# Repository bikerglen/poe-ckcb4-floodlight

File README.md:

# poe-ckcb4-floodlight
Power over Ethernet and Art-Net control for a Color Kinetics Colorburst 4 RGB LED floodlight

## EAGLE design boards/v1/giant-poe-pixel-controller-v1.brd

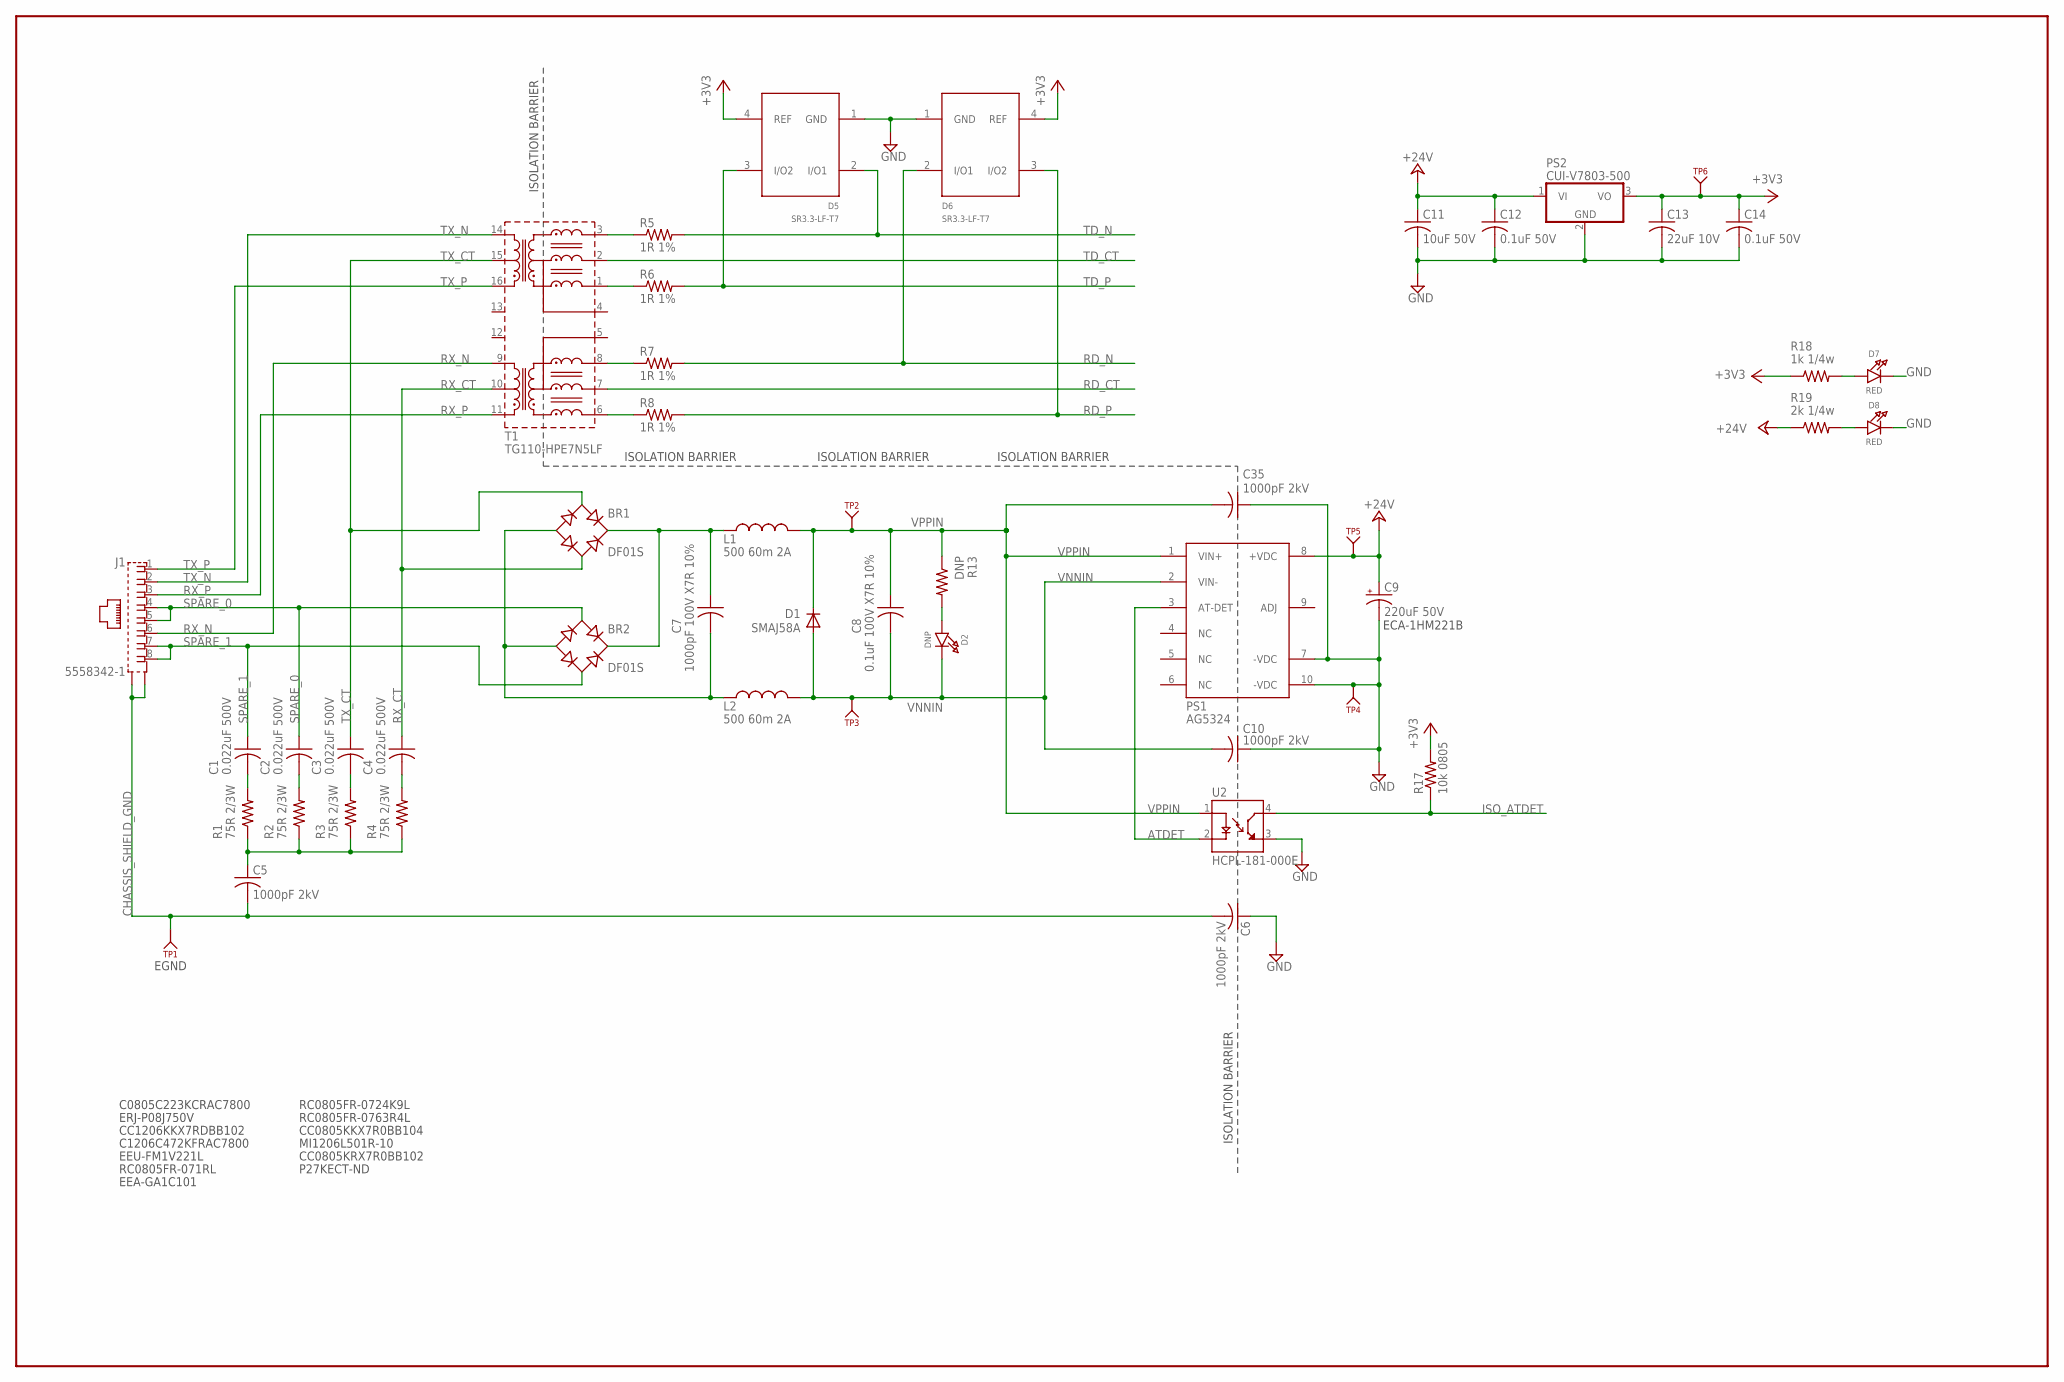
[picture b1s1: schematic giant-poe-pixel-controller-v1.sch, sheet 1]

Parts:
BR1, BR2: DF01S; DFS
C1, C2, C3, C4: 0.022uF 500V; C1206
C5, C6, C10, C35: 1000pF 2kV; C1206K
C7: 1000pF 100V X7R 10%; C0805
C8: 0.1uF 100V X7R 10%; C0805
C9: 220uF 50V; E5-10,5
C11: 10uF 50V; C1210K; MFR_PART_NO C1210C106K5RACTU
C12, C14: 0.1uF 50V; C0805; MFR_PART_NO C1206S104M5RACTU
C13: 22uF 10V; C1206K; MFR_PART_NO C1206C226K8RAC7800
D1: SMAJ58A; DO214AC
D2: DNP; CHIPLED_0805_NOOUTLINE
D5, D6: SR3.3-LF-T7; SOT143B
D7, D8: RED; CHIPLED_0805_NOOUTLINE
J1: 5558342-1; TE_5558342-1
L1, L2: 500 60m 2A; L3216C
PS1: AG5324
PS2: CUI-V7803-500; CUI-78XX-500
R1, R2, R3, R4: 75R 2/3W; R1206
R5, R6, R7, R8: 1R 1%; R0805
R13: DNP; R1206
R17: 10k 0805; R0805
R18: 1k 1/4w; R0805
R19: 2k 1/4w; R0805
T1: TG110-HPE7N5LF; RP-ULTRA
TP1, TP2, TP3, TP4, TP5, TP6: KEYSTONE_500X; KEYSTONE_TP500X
U2: HCPL-181-000E; SOIC254P675X240-4N

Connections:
+3V3: C13.1, C14.1, D5.4 (REF), D6.4 (REF), PS2.3 (VO), R17.2, R18.1, TP6.1; also elsewhere on the board
+24V: C9.+, C11.1, C12.1, PS1.8 (+VDC), PS2.1 (VI), R19.1, TP5.1; also elsewhere on the board
ATDET: PS1.3 (AT-DET), U2.2 (CATHODE)
CHASSIS_SHIELD_GND: C5.2, C6.2, J1.SH1 (S1), J1.SH2 (S2), TP1.1
GND: C6.1, C9.-, C10.1, C11.2, C12.2, C13.2, C14.2, C35.1, D5.1 (GND), D6.1 (GND), D7.C, D8.C, PS1.7 (-VDC), PS1.10 (-VDC), PS2.2 (GND), TP4.1, U2.3 (EMITTER); also elsewhere on the board
ISO_ATDET: R17.1, U2.4 (COLLECTOR); also elsewhere on the board
unnamed: BR1.+, BR2.+, C7.1, L1.1
unnamed: R5.1, T1.3
unnamed: BR1.-, BR2.-, C7.2, L2.1
unnamed: R6.1, T1.1
unnamed: C4.2, R4.2
unnamed: R7.1, T1.8
unnamed: D2.A, R13.2
unnamed: R8.1, T1.6
unnamed: C1.2, R1.2
unnamed: C2.2, R2.2
unnamed: C3.2, R3.2
unnamed: C5.1, R1.1, R2.1, R3.1, R4.1
unnamed: D7.A, R18.2
unnamed: D8.A, R19.2
RD_CT: T1.7; also elsewhere on the board
RD_N: D6.2 (I/O1), R7.2; also elsewhere on the board
RD_P: D6.3 (I/O2), R8.2; also elsewhere on the board
RX_CT: BR1.AC2, C4.1, T1.10
RX_N: J1.6, T1.9
RX_P: J1.3, T1.11
SPARE_0: BR2.AC1, C2.1, J1.4, J1.5
SPARE_1: BR2.AC2, C1.1, J1.7, J1.8
TD_CT: T1.2; also elsewhere on the board
TD_N: D5.2 (I/O1), R5.2; also elsewhere on the board
TD_P: D5.3 (I/O2), R6.2; also elsewhere on the board
TX_CT: BR1.AC1, C3.1, T1.15
TX_N: J1.2, T1.14
TX_P: J1.1, T1.16
VNNIN: C8.2, C10.2, D1.A, D2.C, L2.2, PS1.2 (VIN-), TP3.1
VPPIN: C8.1, C35.2, D1.C, L1.2, PS1.1 (VIN+), R13.1, TP2.1, U2.1 (ANODE)

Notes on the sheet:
C0805C223KCRAC7800
ERJ-P08J750V
CC1206KKX7RDBB102
C1206C472KFRAC7800
EEU-FM1V221L
ISOLATION BARRIER
RC0805FR-071RL
EEA-GA1C101
RC0805FR-0724K9L
RC0805FR-0763R4L
CC0805KKX7R0BB104
MI1206L501R-10
CC0805KRX7R0BB102
P27KECT-ND
EGND
ECA-1HM221B

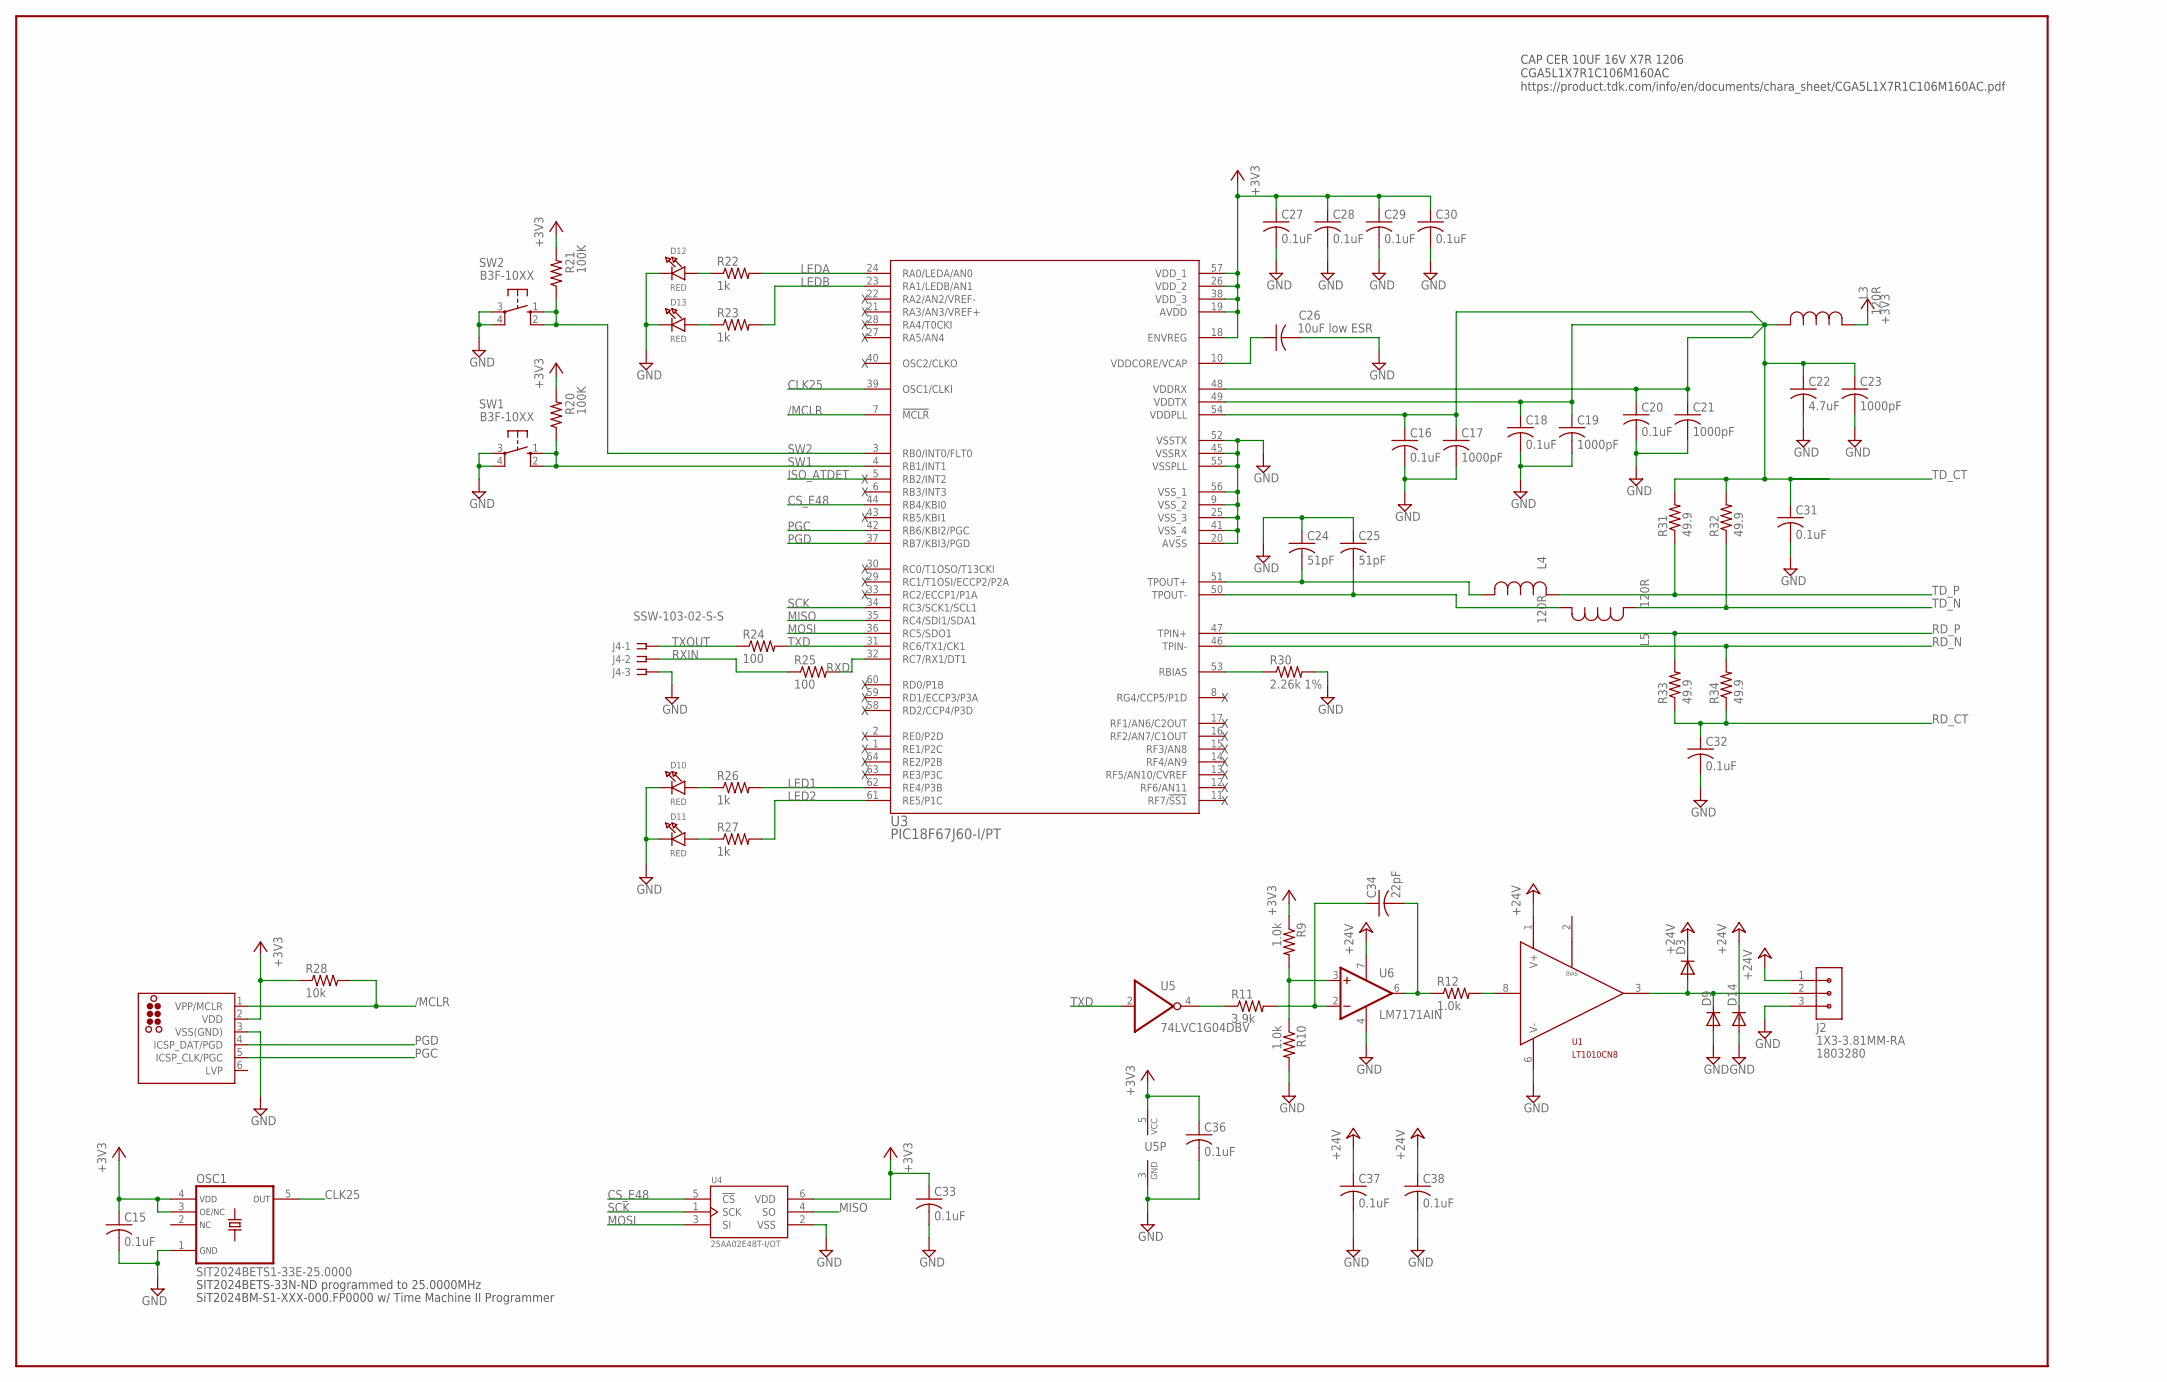
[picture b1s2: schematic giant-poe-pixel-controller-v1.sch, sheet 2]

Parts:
C15, C27, C28, C29, C30, C33, C36, C37, C38: 0.1uF; C0603
C16, C18, C20, C31, C32: 0.1uF; C0805
C17, C19, C21, C23: 1000pF; C0805
C22: 4.7uF; C0805
C24, C25: 51pF; C0805
C26: 10uF low ESR; C1206
C34: 22pF; C0805
D3, D9, D14: DIODE-SOD123; SOD123
D10, D11, D12, D13: RED; CHIPLED_0805_NOOUTLINE
J2: 1X3-3.81MM-RA; CON-PHOENIX-3.81-1X3-RA; MFR_PART_NO 1803280
J3: TC2030-MCP-NL
J4: SSW-103-02-S-S
L3, L4, L5: 120R; IND_1608-M
OSC1: SIT2024BETS1-33E-25.0000; SOT23-5
R9, R10, R12: 1.0k; R0805
R11: 3.9k; R0805
R20, R21: 100K; R0805
R22, R23, R26, R27: 1k; R0805
R24, R25: 100; R0805
R28: 10k; R0805
R30: 2.26k 1%; R0805
R31, R32, R33, R34: 49.9; R0805
SW1, SW2: B3F-10XX
U1: LT1010CN8; DIL08
U3: PIC18F67J60-I/PT; TQFP64_10X10MC
U4: 25AA02E48T-I/OT; SOT95P270X145-6N
U5: 74LVC1G04DBV; SOT23-5
U6: LM7171AIN; SO08

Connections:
+3V3: C15.1, C27.1, C28.1, C29.1, C30.1, C33.1, C36.1, J3.2 (VDD), L3.2, OSC1.3 (OE/NC), OSC1.4 (VDD), R9.1, R20.2, R21.2, R28.1, U3.18 (ENVREG), U3.19 (AVDD), U3.26 (VDD_2), U3.38 (VDD_3), U3.57 (VDD_1), U4.6 (VDD), U5.5 (VCC); also elsewhere on the board
+24V: C37.1, C38.1, D3.C, D14.C, J2.1, U1.1 (V+), U6.7 (V+); also elsewhere on the board
/MCLR: J3.1 (VPP/MCLR), R28.2, U3.7 (!MCLR)
CLK25: OSC1.5 (OUT), U3.39 (OSC1/CLKI)
CS_E48: U3.44 (RB4/KBI0), U4.5 (!CS)
GND: C15.2, C16.2, C17.2, C18.2, C19.2, C20.2, C21.2, C22.2, C23.2, C24.1, C25.1, C26.2, C27.2, C28.2, C29.2, C30.2, C31.2, C32.2, C33.2, C36.2, C37.2, C38.2, D9.A, D10.C, D11.C, D12.C, D13.C, D14.A, J2.3, J3.3 (VSS(GND)), J4.3, OSC1.1 (GND), R10.2, R30.2, SW1.3, SW1.4 (P1), SW2.3, SW2.4 (P1), U1.6 (V-), U3.9 (VSS_2), U3.20 (AVSS), U3.25 (VSS_3), U3.41 (VSS_4), U3.45 (VSSRX), U3.52 (VSSTX), U3.55 (VSSPLL), U3.56 (VSS_1), U4.2 (VSS), U5.3 (GND), U6.4 (V-); also elsewhere on the board
ISO_ATDET: U3.5 (RB2/INT2); also elsewhere on the board
LED1: R26.2, U3.62 (RE4/P3B)
LED2: R27.2, U3.61 (RE5/P1C)
LEDA: R22.2, U3.24 (RA0/LEDA/AN0)
LEDB: R23.2, U3.23 (RA1/LEDB/AN1)
MISO: U3.35 (RC4/SDI1/SDA1), U4.4 (SO)
MOSI: U3.36 (RC5/SDO1), U4.3 (SI)
unnamed: R11.1, U5.4 (O)
unnamed: R30.1, U3.53 (RBIAS)
unnamed: D13.A, R23.1
unnamed: D10.A, R26.1
unnamed: D11.A, R27.1
unnamed: C34.1, R11.2, U6.2 (-IN)
unnamed: R9.2, R10.1, U6.3 (+IN)
unnamed: D12.A, R22.1
unnamed: C34.2, R12.1, U6.6 (OUT)
unnamed: D3.A, D9.C, J2.2, U1.3 (OUTPUT)
unnamed: R12.2, U1.8 (INPUT)
PGC: J3.5 (ICSP_CLK/PGC), U3.42 (RB6/KBI2/PGC)
PGD: J3.4 (ICSP_DAT/PGD), U3.37 (RB7/KBI3/PGD)
RD_CT: C32.1, R33.1, R34.1; also elsewhere on the board
RD_N: R34.2, U3.46 (TPIN-); also elsewhere on the board
RD_P: R33.2, U3.47 (TPIN+); also elsewhere on the board
RXD: R25.2, U3.32 (RC7/RX1/DT1)
RXIN: J4.2, R25.1
SCK: U3.34 (RC3/SCK1/SCL1), U4.1 (SCK)
SW1: R20.1, SW1.1 (S), SW1.2 (S1), U3.4 (RB1/INT1)
SW2: R21.1, SW2.1 (S), SW2.2 (S1), U3.3 (RB0/INT0/FLT0)
TDF_N: C25.2, L5.1, U3.50 (TPOUT-)
TDF_P: C24.2, L4.1, U3.51 (TPOUT+)
TD_CT: C16.1, C17.1, C18.1, C19.1, C20.1, C21.1, C22.1, C23.1, C31.1, L3.1, R31.2, R32.2, U3.48 (VDDRX), U3.49 (VDDTX), U3.54 (VDDPLL); also elsewhere on the board
TD_N: L5.2, R32.1; also elsewhere on the board
TD_P: L4.2, R31.1; also elsewhere on the board
TXD: R24.2, U3.31 (RC6/TX1/CK1), U5.2 (I)
TXOUT: J4.1, R24.1
VDDCORE: C26.1, U3.10 (VDDCORE/VCAP)

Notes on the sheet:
SIT2024BETS-33N-ND programmed to 25.0000MHz
SiT2024BM-S1-XXX-000.FP0000 w/ Time Machine II Programmer
CAP CER 10UF 16V X7R 1206 CGA5L1X7R1C106M160AC https://product.tdk.com/info/en/documents/chara_sheet/CGA5L1X7R1C106M160AC.pdf

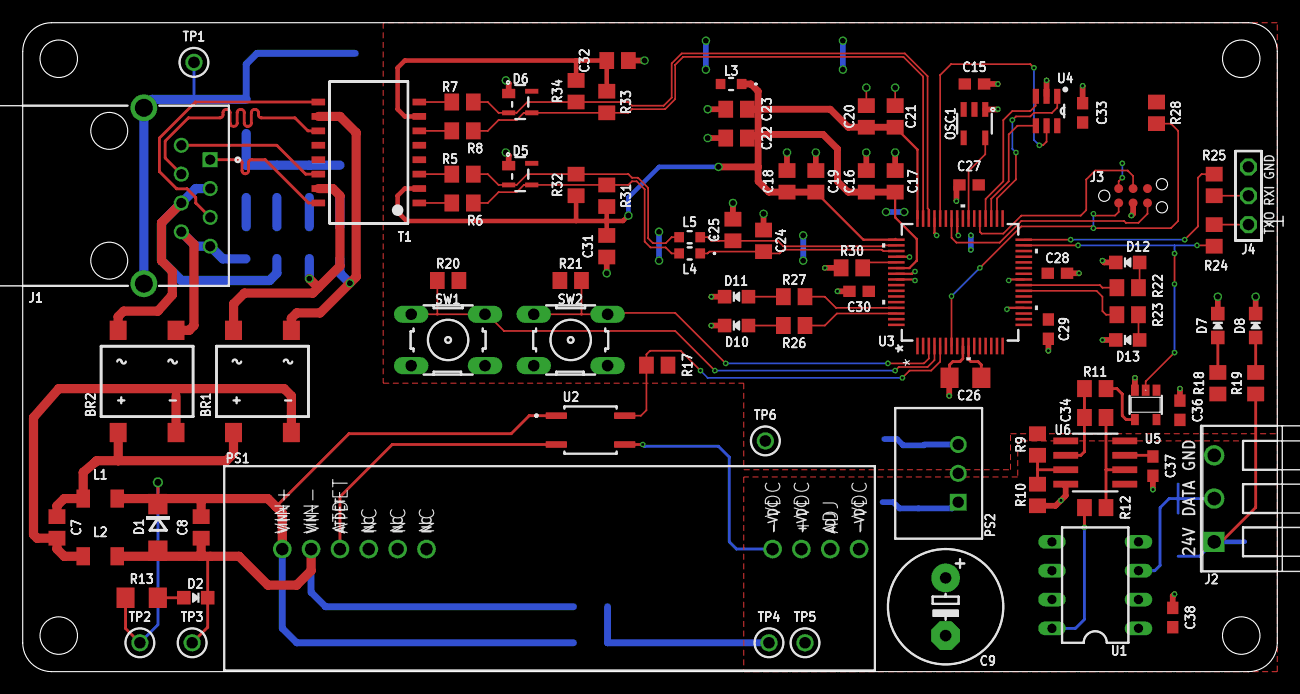
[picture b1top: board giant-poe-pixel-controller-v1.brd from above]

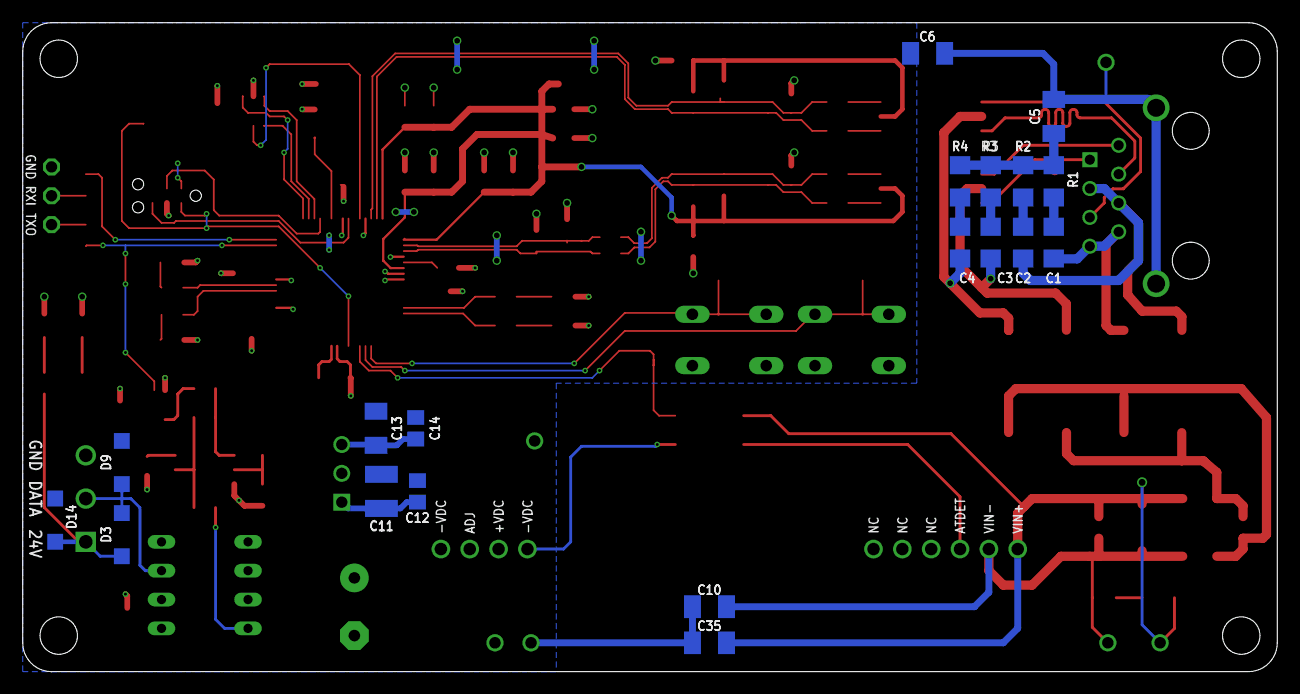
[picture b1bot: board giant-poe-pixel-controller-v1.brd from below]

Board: 2 copper layers, 110.5 x 57.1 mm, 110 parts (19 on the bottom side), 68 nets.

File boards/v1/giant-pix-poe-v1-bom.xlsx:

Qty | Parts | Description | Size | Mfr | Mfr Part # | Dist | Dist Part 3 | Notes
2 | BR1, BR2 | BRIDGE RECT 1P 100V 1.5A SMD 4SDIP | --- | On Semiconductor | DF01S | Digi-Key | DF01SCT-ND
4 | C1, C2, C3, C4 | CAP CER 0.022uF 500V 10% X7R SMD 1206 | 1206 | Johanson Dielectrics | 501R18W223KV4E | Digi-Key | 709-1028-1-ND
4 | C5, C6, C10, C35 | CAP CER 1000pF 2KV 10% X7R SMD 1206 | 1206 | Johanson Dielectrics | 202R18W102KV4E | Digi-Key | 709-1036-1-ND
1 | C7 | CAP CER 1000PF 100V 10% X7R SMD 0805 | 0805 | Kemet | C0805C102K1RACTU | Digi-Key | 399-1148-1-ND
1 | C8 | CAP CER 0.1uF 100V 10% X7R SMD 0805 | 0805 | Yageo | CC0805KKX7R0BB104 | Digi-Key | 311-2083-1-ND
1 | C9 | CAP ALUM 220uF 20% 50V RADIAL | E5-10,5 | Panasonic | ECA-1HM221 | Digi-Key | P5183-ND
1 | C11 | CAP CER 10uF 50V 10% X7R SMD 1210 | 1210 | Kemet | C1210C106K5RACTU | Digi-Key | 399-11629-1-ND
7 | C12, C14, C16, C18, C20, C31, C32 | CAP CER 0.1u 50V 10% X7R SMD 0805 | 0805 | Kemet | C0805C104K5RACTU | Digi-Key | 399-1170-1-ND
1 | C13 | CAP CER 22uF 10V 10% X7R SMD 1206 | 1206 | Kemet | C1206C226K8RAC7800 | Digi-Key | 399-11947-1-ND
9 | C15, C27, C28, C29, C30, C33, C36, C37, C38 | CAP CER 0.1uF 50V 20% X7R SMD 0603 | 0603 | TDK | C1608X7R1H104M | Digi-Key | 445-5098-1-ND
4 | C17, C19, C21, C23 | CAP CER 1000pF 50V 20% X7R SMD 0805 | 0805 | Kemet | C0805C102M5RACTU | Digi-Key | 399-1146-1-ND
1 | C22 | CAP CER 4.7uF 10V 10% X5R SMD 0805 | 0805 | Kemet | C0805C475K8PACTU | Digi-Key | 399-3133-1-ND
2 | C24, C25 | CAP CER 51pF 50V 5% NP0 SMD 0805 | 0805 | Yageo | CC0805JRNPO9BN510 | Digi-Key | 311-4239-1-ND
1 | C26 | CAP CER 10uF 16V 20% X7R SMD 1206 | 1206 | TDK | CGA5L1X7R1C106M160AC | Digi-Key | 445-12903-1-ND
1 | C34 | CAP CER 22pF 50V 10% X7R SMD 0805 | 0805 | Kemet | C0805C220K5RAC7800 | Digi-Key | 399-17626-1-ND
1 | D1 | TVS DIODE 58V 121V SMA | --- | ST Microelectronics | SMAJ58A-TR | Digi-Key | 497-3508-1-ND
7 | D2, D7, D8, D10, D11, D12, D13 | LED RED CLEAR CHIP SMD 0805 | 0805 | Kingbright | APHCM2012SURCK-F01 | Digi-Key | 754-1097-1-ND
3 | D3, D9, D14 | DIODE GEN PURP 100V 150MA SOD123 | SOD-123 | Micro Commercial Co | 1N4148W-TP | Digi-Key | 1N4148WTPMSCT-ND
2 | D5, D6 | TVS DIODE 3.3V 7V SOT143 | --- | Bourns | CD143A-SR3.3 | Digi-Key | CD143A-SR3.3CT-ND
1 | J1 | CONN MOD JACK 8P8C R/A SHIELDED | --- | TE Connectivity | 5558342-1 | Digi-Key | A31466-ND
1 | J2 | TERM BLOCK HDR 3POS 90DEG 3.81MM | --- | Phoenix | 1803280 | Digi-Key | 277-1207-ND
1 | J3 | TAG CONNECT ICSP PCB PADS | --- | --- | --- | --- | ---
1 | J4 | CONN HEADER VERT 3POS 2.54MM | --- | Samtec | TSW-103-07-G-S | Digi-Key | SAM1029-03-ND
2 | L1, L2 | FERRITE BEAD 500 OHM 1206 1LN | M3216 | Laird | MI1206L501R-10 | Digi-Key | 240-2407-1-ND
3 | L3, L4, L5 | FERRITE BEAD 120 OHM 0603 1LN | M1608 | TDK | MMZ1608B121CTAH0 | Digi-Key | 445-2164-1-ND
1 | OSC1 | MEMS OSC PROG XO LVCMOS 3.3V | --- | Si Time | SIT2024BETS-33N | Digi-Key | SIT2024BETS-33N-ND | 25.0000 MHz
1 | PS1 | POE+ 802.3AT MODULE 24V SIP | --- | Silvertel | AG5324
1 | PS2 | DC DC CONVERTER 3.3V 1.65W | --- | Cui | V7803-500 | Digi-Key | 102-1708-ND
4 | R1, R2, R3, R4 | RES SMD 75 OHM 5% 2/3W 1206 | 1206 | Panasonic | ERJ-P08J750V | Digi-Key | P75ALCT-ND
4 | R5, R6, R7, R8 | RES SMD 1 OHM 1% 1/8W 0805 | 0805 | Panasonic | ERJ-6RQF1R0V | Digi-Key | P1.0DCT-ND
8 | R9,R10,R12,R18, R22, R23, R26, R27 | RES SMD 1K OHM 5% 1/8W 0805 | 0805 | Panasonic | ERJ-6GEYJ102V | Digi-Key | P1.0KACT-ND
1 | R11 | RES SMD 3.9K OHM 5% 1/8W 0805 | 0805 | Panasonic | ERJ-6GEYJ392V | Digi-Key | P3.9KACT-ND
1 | R13 | RES SMD 27K OHM 5% 1/4W 1206 | 1206 | Panasonic | ERJ-8GEYJ273V | Digi-Key | P27KECT-ND
2 | R17, R28 | RES SMD 10K OHM 5% 1/8W 0805 | 0805 | Panasonic | ERJ-6GEYJ103V | Digi-Key | P10KACT-ND
1 | R19 | RES SMD 2K OHM 5% 1/8W 0805 | 0805 | Panasonic | ERJ-6GEYJ202V | Digi-Key | P2KACT-ND
2 | R20, R21 | RES SMD 100K OHM 5% 1/8W 0805 | 0805 | Panasonic | ERJ-6GEYJ104V | Digi-Key | P100KACT-ND
2 | R24, R25 | RES SMD 100 OHM 5% 1/8W 0805 | 0805 | Panasonic | ERJ-6GEYJ101V | Digi-Key | P100ACT-ND
1 | R30 | RES SMD 2.26K OHM 1% 1/8W 0805 | 0805 | Panasonic | ERJ-6ENF2261V | Digi-Key | P2.26KCCT-ND
4 | R31, R32, R33, R34 | RES SMD 49.9 OHM 1% 1/8W 0805 | 0805 | Panasonic | ERJ-6ENF49R9V | Digi-Key | P49.9CCT-ND
2 | SW1, SW2 | SWITCH TACTILE SPST-NO 0.05A 24V | --- | Omron | B3F-1000 | Digi-Key | SW400-ND
1 | T1 | 10/100BASE-TX SMD Ultra PoE+ | --- | Halo Electronics | TG110-HPE7N5LF | Mouser | 493-TG110-HPE7N5LF
6 | TP1, TP2, TP3, TP4, TP5, TP6 | PC TEST POINT MINIATURE | --- | Keystone | 5000 | Digi-Key | 36-5000-ND
1 | U1 | IC BUFFER 1 CIRCUIT 8DIP | 8DIP | Linear | LT1010CN8#PBF | Digi-Key | LT1010CN8#PBF-ND
1 | U2 | OPTOISO 3.75KV TRANSISTOR 4SOIC | SO-4 | Broadcom | HCPL-181-000E | Digi-Key | 516-1646-1-ND
1 | U3 | IC MCU 8BIT 128KB FLASH 64TQFP | TQFP-64 | Microchip | PIC18F67J60-I/PT | Digi-Key | PIC18F67J60-I/PT-ND
1 | U4 | IC EEPROM 2K SPI 10MHZ SOT23-6 | SOT23-6 | Microchip | 25AA02E48T-I/OT | Digi-Key | 25AA02E48T-I/OTCT-ND
1 | U5 | IC INVERTER 1CH 1-INP SOT23-5 | SOT23-5 | TI | SN74LVC1G04DBVR | Digi-Key | 296-11599-1-ND
1 | U6 | IC OPAMP VFB 1 CIRCUIT 8SOIC | SO-8 | TI | LM7171AIMX/NOPB | Digi-Key | 296-35428-1-ND

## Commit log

2020-02-17 added schematic, board, and bill of materials
2020-02-17 adding software

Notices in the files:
parts and their libraries:
tag-connect: ©2009 ROFA.cz - modified and updated by Robert Darlington ‹rdarlington@gmail.com›
microbuilder: This work is placed in the public domain, and may be freely used for commercial and non-commercial work with the following conditions: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
